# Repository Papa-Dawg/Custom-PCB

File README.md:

# Papa Dawg Custom PCB

## Overview
This is a custom PCB designed in **KiCad 9.0**. It is an Arduino-compatible controller featuring:
* **7-Segment Display:** Integrated layout for numerical feedback.
* **Breakout Ports:** Easy access to Port B, C, and D for prototyping.
* **Onboard Controls:** Includes a Reset button and a programmable button.
* **Power Management:** Integrated On/Off toggle and LED indicator.

## Project Structure
* `/Arduino1.kicad_sch`: Schematic design.
* `/Arduino1.kicad_pcb`: Board layout and routing.
* `3-D Model.png`: Visual render of the completed board.

## Status
- [x] Schematic Design
- [x] PCB Layout
- [ ] Fabrication / Physical Testing

## License
This project is licensed under the [CERN Open Hardware License](https://ohwr.org/project/cernohl/wikis/Documents/CERN-OHL-version-2).

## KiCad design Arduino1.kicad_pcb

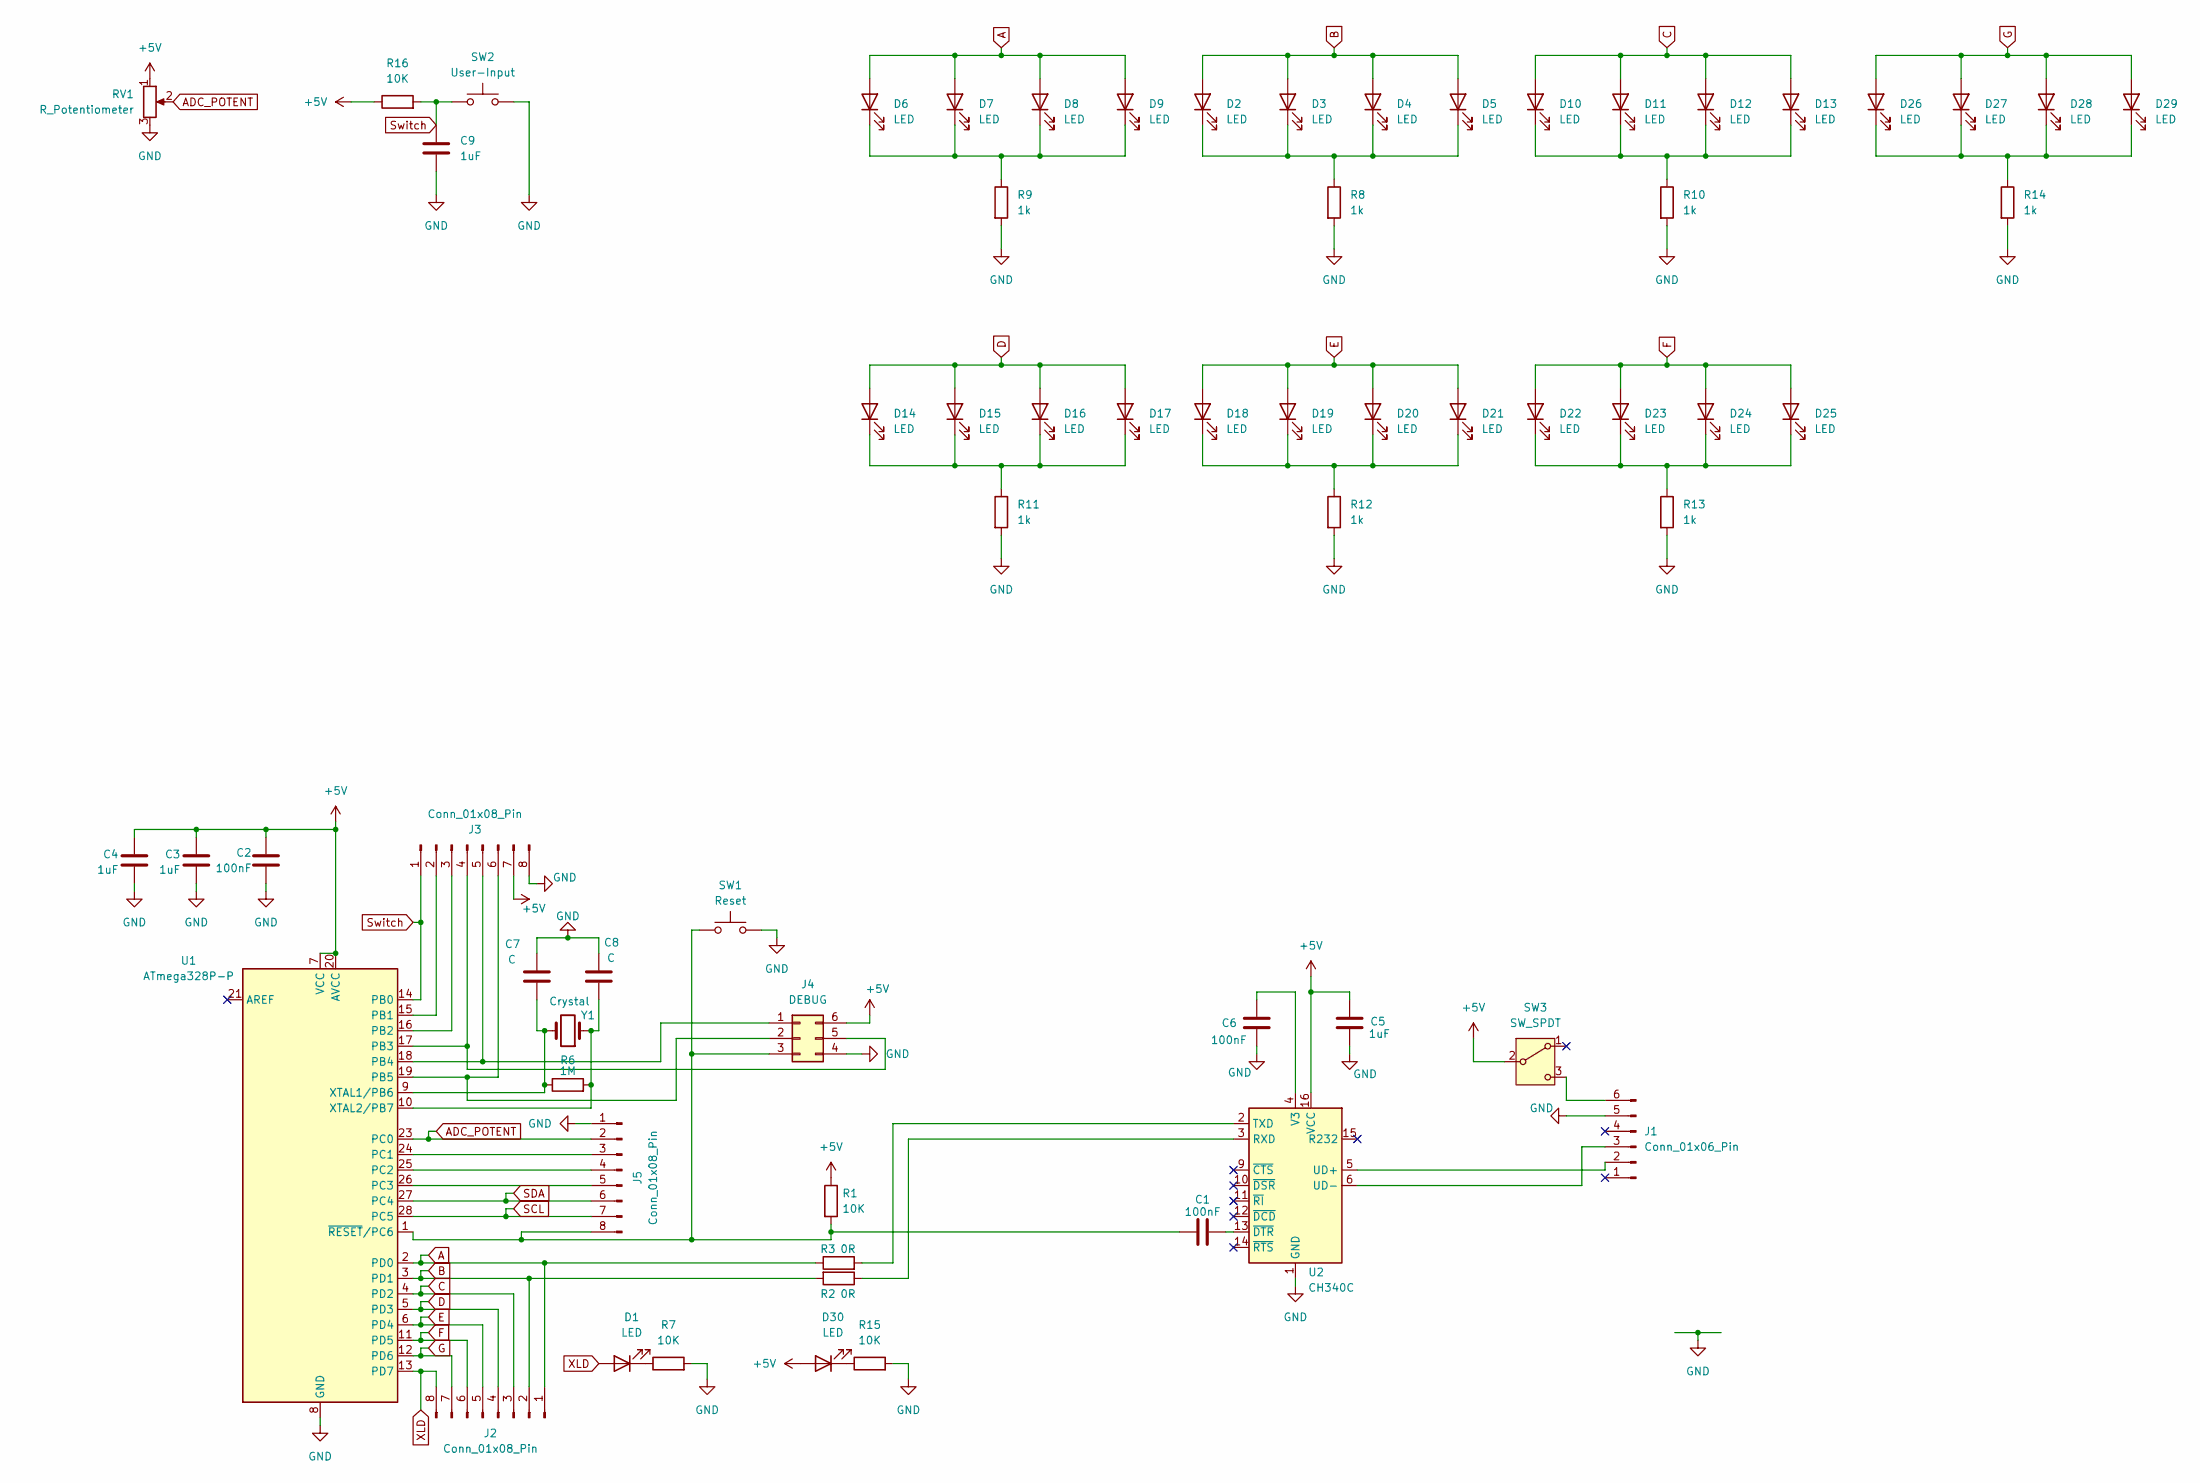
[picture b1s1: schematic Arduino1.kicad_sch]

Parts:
C1, C2, C6: 100nF; LED_1206_3216Metric
C3, C4, C5, C9: 1uF; LED_1206_3216Metric
C7, C8: C; LED_1206_3216Metric
D1, D2, D3, D4, D5, D6, D7, D8, D9, D10, D11, D12, D13, D14, D15, D16, D17, D18, D19, D20, D21, D22, D23, D24, D25, D26, D27, D28, D29, D30: LED; LED_1206_3216Metric
J1: Conn_01x06_Pin; PinSocket_1x06_P2.54mm_Vertical
J2, J3, J5: Conn_01x08_Pin; PinHeader_1x08_P2.54mm_Vertical
J4: DEBUG; PinHeader_2x03_P2.54mm_Vertical
R1, R7, R15, R16: 10K; R_0805_2012Metric
R2, R3: 0R; R_0805_2012Metric
R6: 1M; R_0805_2012Metric
R8, R9, R10, R11, R12, R13, R14: 1k; R_0805_2012Metric
RV1: R_Potentiometer; PinHeader_1x03_P2.54mm_Vertical
SW1: Reset; SW_SPST_B3U-1000P-B
SW2: User-Input; SW_SPST_B3U-1000P-B
SW3: SW_SPDT; PinHeader_1x03_P2.54mm_Vertical
U1: ATmega328P-P; DIP-28_W7.62mm
U2: CH340C; SOIC-16_3.9x9.9mm_P1.27mm
Y1: Crystal; Crystal_HC49-U_Vertical

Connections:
+5V: C2.1, C3.1, C4.1, C5.1, D30.2 (A), J3.7, J4.6, R1.1, R16.1, RV1.1, SW3.2 (B), U1.7 (VCC), U1.20 (AVCC), U2.16 (VCC)
A: D6.2 (A), D7.2 (A), D8.2 (A), D9.2 (A), J2.1, R3.1, U1.2 (PD0)
ADC_POTENT: J5.2, RV1.2, U1.23 (PC0)
B: D2.2 (A), D3.2 (A), D4.2 (A), D5.2 (A), J2.2, R2.2, U1.3 (PD1)
C: D10.2 (A), D11.2 (A), D12.2 (A), D13.2 (A), J2.3, U1.4 (PD2)
D: D14.2 (A), D15.2 (A), D16.2 (A), D17.2 (A), J2.4, U1.5 (PD3)
E: D18.2 (A), D19.2 (A), D20.2 (A), D21.2 (A), J2.5, U1.6 (PD4)
F: D22.2 (A), D23.2 (A), D24.2 (A), D25.2 (A), J2.6, U1.11 (PD5)
G: D26.2 (A), D27.2 (A), D28.2 (A), D29.2 (A), J2.7, U1.12 (PD6)
GND: C2.2, C3.2, C4.2, C5.2, C6.2, C7.1, C8.1, C9.2, J1.5, J3.8, J4.4, J5.1, R7.2, R8.2, R9.2, R10.2, R11.2, R12.2, R13.2, R14.2, R15.2, RV1.3, SW1.2, SW2.2, U1.8 (GND), U1.22 (GND), U2.1 (GND); also elsewhere on the board
unnamed: D1.1 (K), R7.1
unnamed: D2.1 (K), D3.1 (K), D4.1 (K), D5.1 (K), R8.1
unnamed: D6.1 (K), D7.1 (K), D8.1 (K), D9.1 (K), R9.1
unnamed: D10.1 (K), D11.1 (K), D12.1 (K), D13.1 (K), R10.1
unnamed: D14.1 (K), D15.1 (K), D16.1 (K), D17.1 (K), R11.1
unnamed: D18.1 (K), D19.1 (K), D20.1 (K), D21.1 (K), R12.1
unnamed: D22.1 (K), D23.1 (K), D24.1 (K), D25.1 (K), R13.1
unnamed: D26.1 (K), D27.1 (K), D28.1 (K), D29.1 (K), R14.1
unnamed: D30.1 (K), R15.1
unnamed: J1.2, U2.5 (UD+)
unnamed: J1.3, U2.6 (UD-)
unnamed: J1.6, SW3.3 (C)
unnamed: J3.2, U1.15 (PB1)
unnamed: J3.3, U1.16 (PB2)
unnamed: J3.4, J4.5, U1.17 (PB3)
unnamed: J3.5, J4.1, U1.18 (PB4)
unnamed: J3.6, J4.2, U1.19 (PB5)
unnamed: C1.1, J4.3, J5.8, R1.2, SW1.1, U1.1 (~RESET/PC6)
unnamed: J5.3, U1.24 (PC1)
unnamed: J5.4, U1.25 (PC2)
unnamed: J5.5, U1.26 (PC3)
unnamed: C7.2, R6.1, U1.9 (XTAL1/PB6), Y1.2
unnamed: C8.2, R6.2, U1.10 (XTAL2/PB7), Y1.1
unnamed: R2.1, U2.3 (RXD)
unnamed: R3.2, U2.2 (TXD)
unnamed: C6.1, U2.4 (V3)
unnamed: C1.2, U2.13 (~DTR)
SCL: J5.7, U1.28 (PC5)
SDA: J5.6, U1.27 (PC4)
Switch: C9.1, J3.1, R16.2, SW2.1, U1.14 (PB0)
XLD: D1.2 (A), J2.8, U1.13 (PD7)

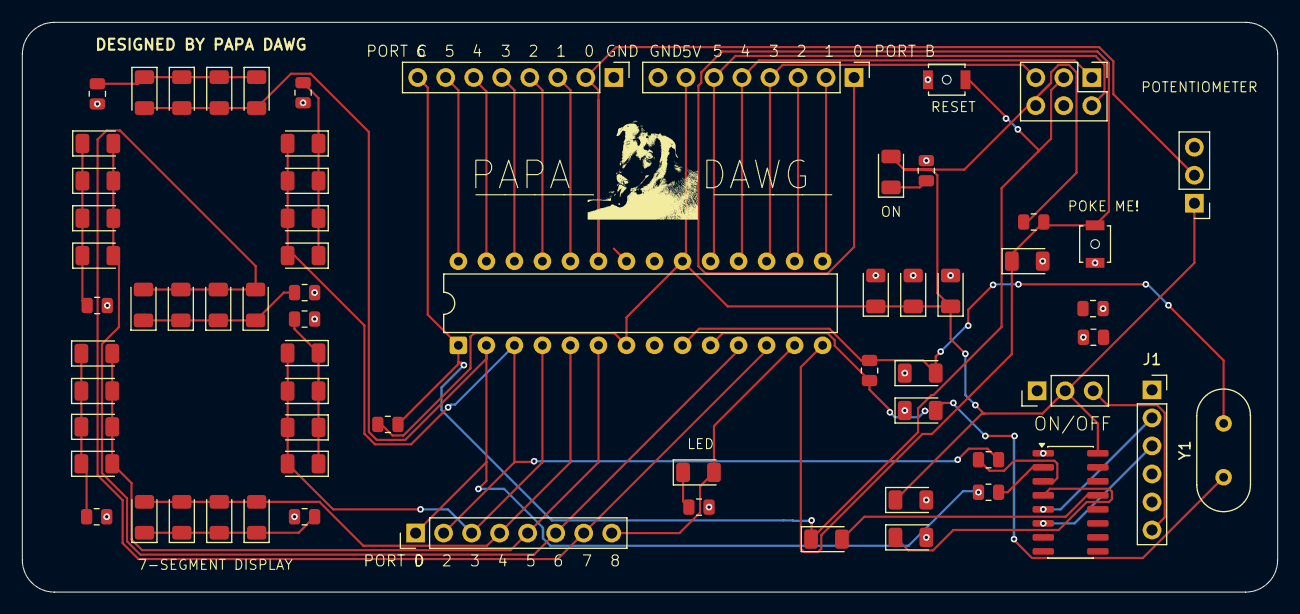
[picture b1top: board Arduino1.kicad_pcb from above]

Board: 2 copper layers, 113.8 x 51.6 mm, 67 parts (0 on the bottom side), 41 nets.

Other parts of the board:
R4, R5: 5K1; R_0805_2012Metric

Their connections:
GND: R4.1, R5.2; also elsewhere on the board

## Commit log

2026-05-08 Initial Commit: Custom PCB
2026-05-08 Add files via upload
    3-D Model of PCB Design
